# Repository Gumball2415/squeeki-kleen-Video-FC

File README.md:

# squeeki-kleen-Video-FC

An open source hardware external composite video bypass preamplifier modboard
for the Famicom/NES

## About

I made a compact daughterboard composite video output based on the
[composite amplifier circuit from the AV Famicom](https://www.nesdev.org/wiki/PPU_pinout#Composite_Video_Output).
This is designed to make AV modding RF-only consoles such as the RF Famicom and the Toploading NES-101 compact and simple.

## How to install

TODO: image demonstrations.

1. If your board does not have tented vias, cover the area underneath the PPU with insulating tape. Be sure to also cover underneath the MMCX connector footprint to avoid shorts.
2. To reduce stray inductive connections, isolate pin 21 of the PPU by cutting any traces connecting to it as close to the through-hole pad as much as possible.
3. If needed, add additional bypass capacitors in the empty C3 and C4 footprints.

## PCB specifications

Note that this project is optimized for JLCPCB manufacturing.

- 2 layers
- 50.80 x 17.78 mm
- 0.8 mm thickness (or 1.60 mm if you plan to attach the MMCX connector)
- Any surface finish
- Any soldermask/silkscreen color
- Tented vias
	- alternatively, cover area under board with kapton/insulative tape

## License

This is licensed under the [TAPR Open Hardware Licence](https://tapr.org/the-tapr-open-hardware-license/). Copyright Persune 2025.

## Credits

Special thanks to:
- The NESDev community for advice and help
- lidnariq for advice
- Finny (grievre/arreffem) for inspiration
- j4m13c0 for testing the board (and notifying me of Q1 pinout error!)

## Support

If you enjoy this project or find it helpful, please support me using the links below!

- 
- [Patreon](https://patreon.com/persune)

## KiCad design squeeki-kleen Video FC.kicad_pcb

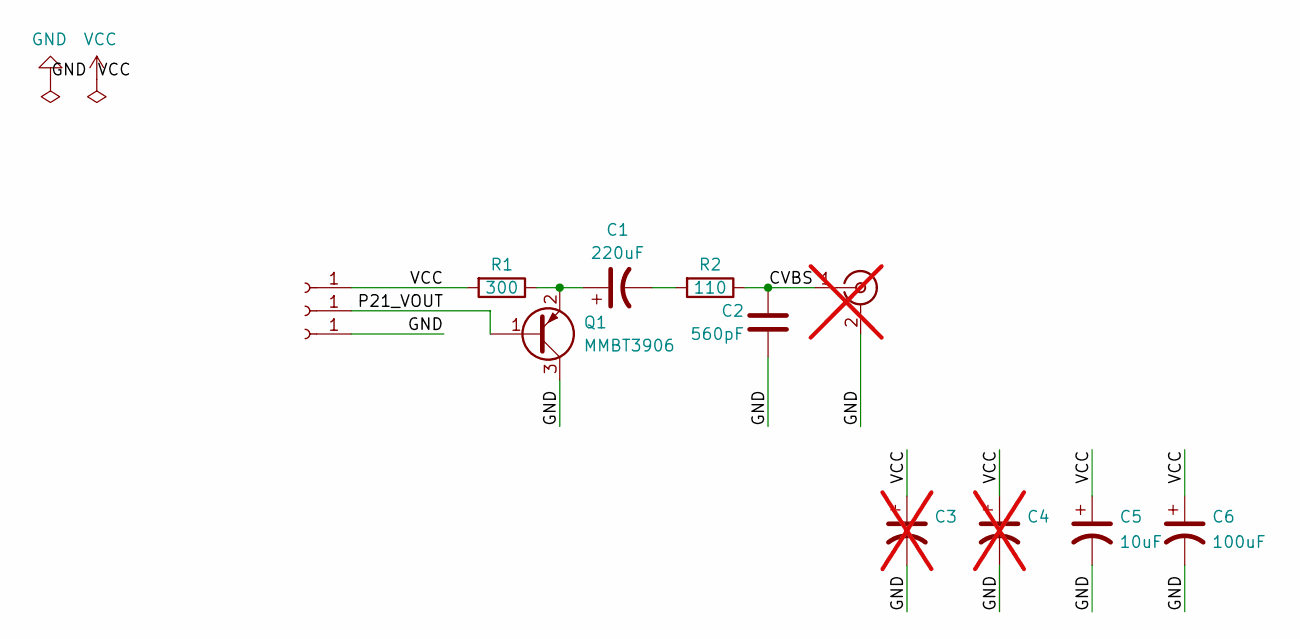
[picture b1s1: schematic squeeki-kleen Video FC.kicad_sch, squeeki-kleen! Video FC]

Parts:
C1: 220uF; CP_Elec_6.3x5.4; LCSC C72494
C2: 560pF; C_0805_2012Metric; LCSC C527188
C3, C4: CP_EIA-3216-18_Kemet-A; LCSC C1508940; not fitted
C5: 10uF; CP_EIA-3216-18_Kemet-A; LCSC C1508940
C6: 100uF; CP_Elec_6.3x4.5; LCSC C5374788
J1: VCC; THT_Hole
J2: VOUT; THT_Hole
J3: GND; THT_Hole
J4: Conn_Coaxial; MMCX_Molex_73415-0961_Horizontal_0.8mm-PCB; not fitted
Q1: MMBT3906; SOT-23; LCSC C2891809
R1: 300; R_0805_2012Metric; LCSC C17617
R2: 110; R_0805_2012Metric; LCSC C229072

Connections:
/CVBS: C2.1, J4.1 (In), R2.1
/P21_VOUT: J2.1, Q1.1 (B)
GND: C2.2, C3.2, C4.2, C5.2, C6.2, J3.1, J4.2 (Ext), Q1.3 (C)
unnamed: C1.2, R2.2
unnamed: C1.1, Q1.2 (E), R1.1
VCC: C3.1, C4.1, C5.1, C6.1, J1.1, R1.2

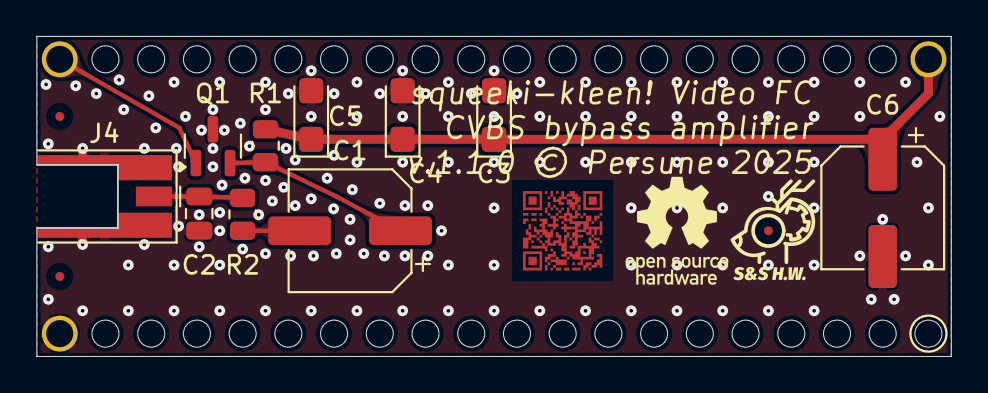
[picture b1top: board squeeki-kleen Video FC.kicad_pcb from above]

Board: 2 copper layers, 50.8 x 17.8 mm, 16 parts (0 on the bottom side), 6 nets.

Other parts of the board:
svg2mod: G***; qr
svg2mod#2: G***; maustech icon fiducial 0-50mm 1-50mm
svg2mod#3: G***; oshw-logo 6x6mm

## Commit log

2022-12-21 Initial board
2022-12-21 Fix readme image
2022-12-21 Fix bullet points
2023-03-06 Big changes
    - Fix MMBT3906 pinout
    - Use NPTH instead of edge cut circles
    - Update silkscreen art
    - Add 100uF electrolytic capacitor for power
2023-03-06 Update revision date
2023-03-06 Update PCB image
2023-04-05 Update silkscreen art to add QR code
2023-04-05 Add funding
2023-04-05 Implement four-module quiet zone in QR code
2023-04-05 Update README image
2023-04-07 Add version number to PCB
2025-02-23 Compact component placement, add teardrops
2025-02-23 Widen holes, add extra empty capacitor footprints

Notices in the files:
squeeki-kleen Video FC.kicad_pcb:
v.1.1.0 © Persune 2025
